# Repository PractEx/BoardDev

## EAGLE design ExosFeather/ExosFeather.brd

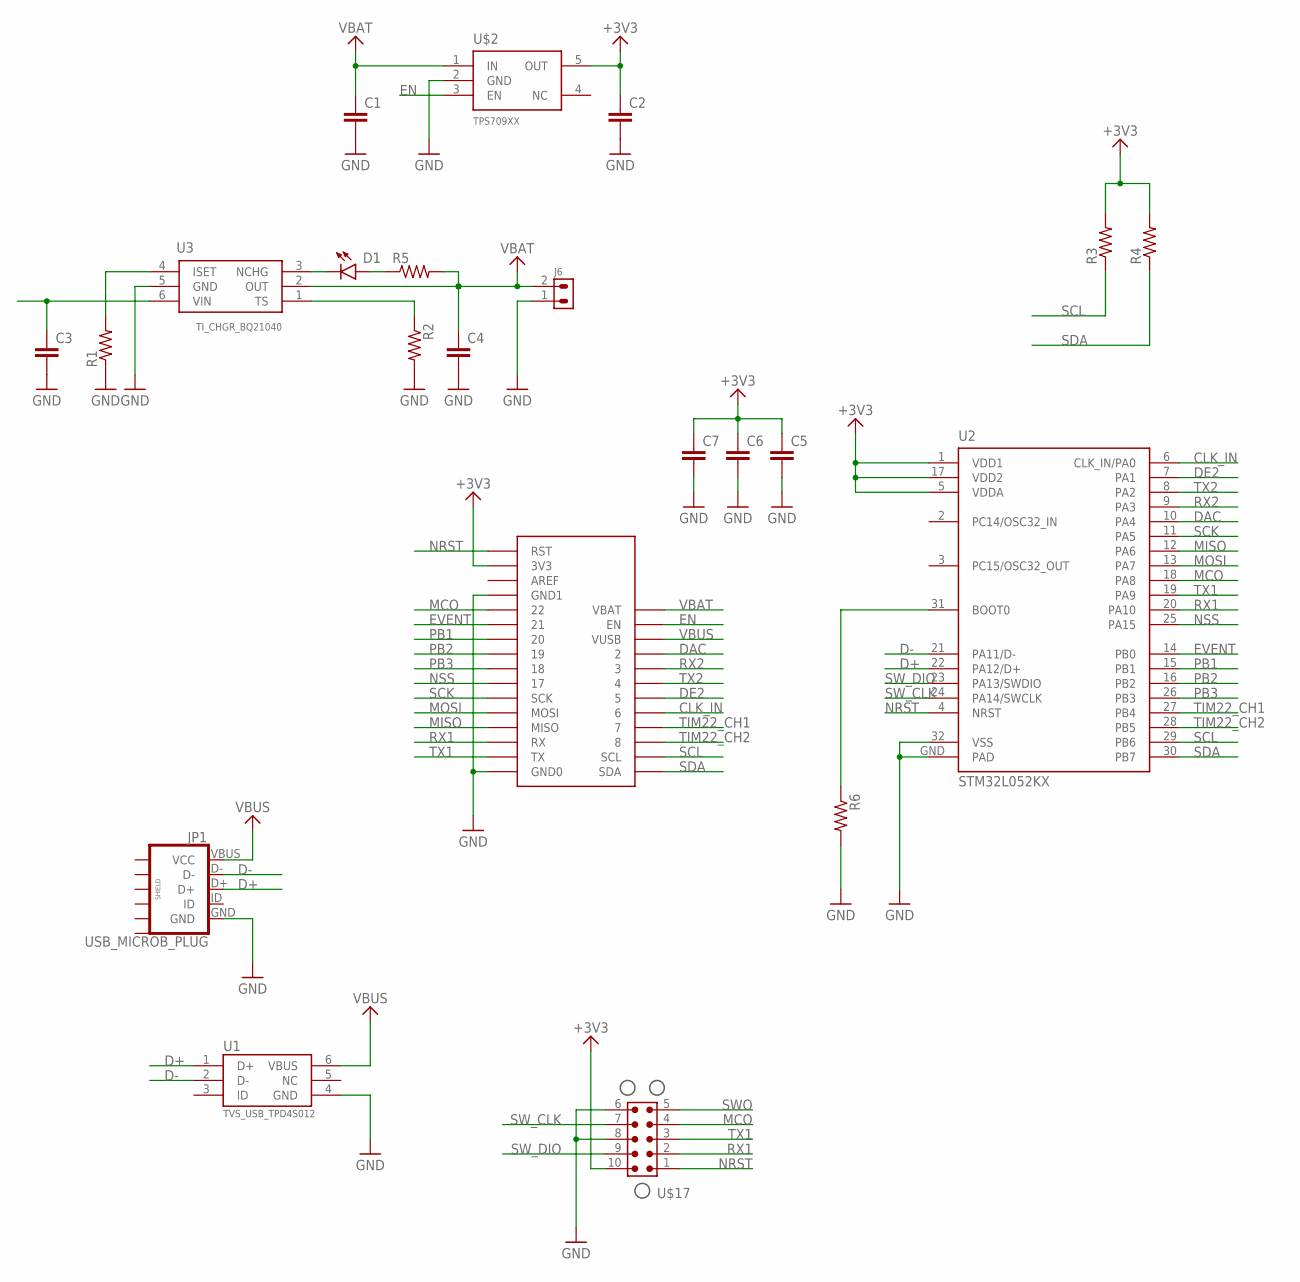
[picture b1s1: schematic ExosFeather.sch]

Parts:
C1, C2, C3, C4, C5, C6, C7: 0603_CAP; 0603
D1: 0603_LED
J6: CONN_2X1_JST_PA
JP1: USB_MICROB_PLUG; USB-MICROB
R1, R2, R3, R4, R5, R6: 0603_RES; 0603
U1: TVS_USB_TPD4S012; USB_TVS_TPD4S012
U2: STM32L052KX; STM32_QFN_32_5X5
U3: TI_CHGR_BQ21040; SOT-23-6_TI
U$1: FEATHER_PINOUT_FULL
U$2: TPS709XX; SOT23-5
U$17: TC_2050_IDC_TOP; TC_2050_IC_TOP

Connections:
+3V3: C2.P$1 (1), C5.P$1 (1), C6.P$1 (1), C7.P$1 (1), R3.P$2 (2), R4.P$2 (2), U2.1 (VDD1), U2.5 (VDDA), U2.17 (VDD2), U$1.P$27 (3V3), U$2.5 (OUT), U$17.10
CLK_IN: U2.6 (CLK_IN/PA0), U$1.P$8 (6)
D+: JP1.D+, U1.1 (D+), U2.22 (PA12/D+)
D-: JP1.D-, U1.2 (D-), U2.21 (PA11/D-)
DAC: U2.10 (PA4), U$1.P$4 (2)
DE2: U2.7 (PA1), U$1.P$7 (5)
EN: U$1.P$2 (EN), U$2.3 (EN)
EVENT: U2.14 (PB0), U$1.P$23 (21)
GND: C1.P$2 (2), C2.P$2 (2), C3.P$2 (2), C4.P$2 (2), C5.P$2 (2), C6.P$2 (2), C7.P$2 (2), J6.1, JP1.GND, R1.P$1 (1), R2.P$2 (2), R6.P$2 (2), U1.4 (GND), U2.32 (VSS), U2.GND (PAD), U3.5 (GND), U$1.P$13 (GND0), U$1.P$25 (GND1), U$2.2 (GND), U$17.6, U$17.8
MCO: U2.18 (PA8), U$1.P$24 (22), U$17.4
MISO: U2.12 (PA6), U$1.P$16 (MISO)
MOSI: U2.13 (PA7), U$1.P$17 (MOSI)
unnamed: R6.P$1 (1), U2.31 (BOOT0)
unnamed: R2.P$1 (1), U3.1 (TS)
unnamed: R1.P$2 (2), U3.4 (ISET)
unnamed: D1.P$2 (C), U3.3 (NCHG)
unnamed: D1.P$1 (A), R5.P$1 (1)
NRST: U2.4 (NRST), U$1.P$28 (RST), U$17.1
NSS: U2.25 (PA15), U$1.P$19 (17)
PB1: U2.15 (PB1), U$1.P$22 (20)
PB2: U2.16 (PB2), U$1.P$21 (19)
PB3: U2.26 (PB3), U$1.P$20 (18)
RX1: U2.20 (PA10), U$1.P$15 (RX), U$17.2
RX2: U2.9 (PA3), U$1.P$5 (3)
SCK: U2.11 (PA5), U$1.P$18 (SCK)
SCL: R3.P$1 (1), U2.29 (PB6), U$1.P$11 (SCL)
SDA: R4.P$1 (1), U2.30 (PB7), U$1.P$12 (SDA)
SWO: U$17.5
SW_CLK: U2.24 (PA14/SWCLK), U$17.7
SW_DIO: U2.23 (PA13/SWDIO), U$17.9
TIM22_CH1: U2.27 (PB4), U$1.P$9 (7)
TIM22_CH2: U2.28 (PB5), U$1.P$10 (8)
TX1: U2.19 (PA9), U$1.P$14 (TX), U$17.3
TX2: U2.8 (PA2), U$1.P$6 (4)
VBAT: C1.P$1 (1), C4.P$1 (1), J6.2, R5.P$2 (2), U3.2 (OUT), U$1.P$1 (VBAT), U$2.1 (IN)
VBUS: C3.P$1 (1), JP1.VBUS (VCC), U1.6 (VBUS), U3.6 (VIN), U$1.P$3 (VUSB)

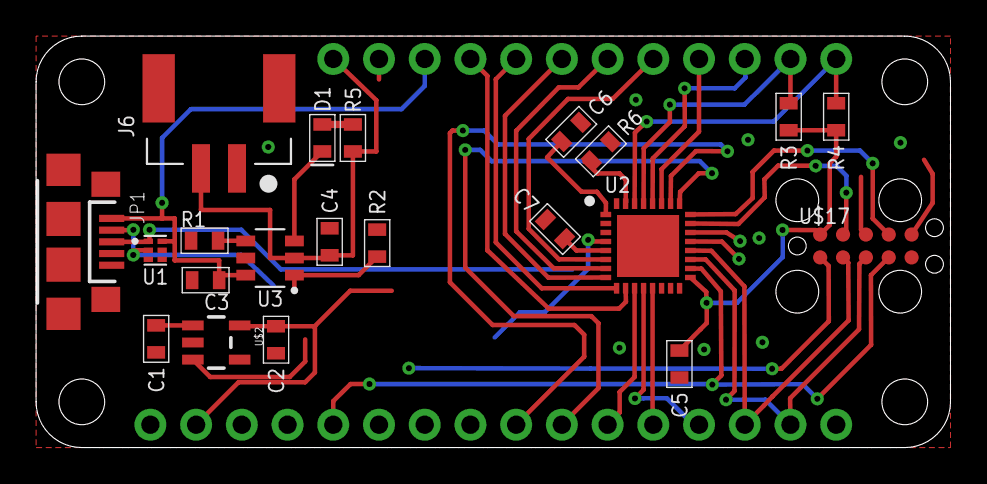
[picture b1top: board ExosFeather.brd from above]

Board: 2 copper layers, 50.8 x 22.9 mm, 22 parts (0 on the bottom side), 35 nets.

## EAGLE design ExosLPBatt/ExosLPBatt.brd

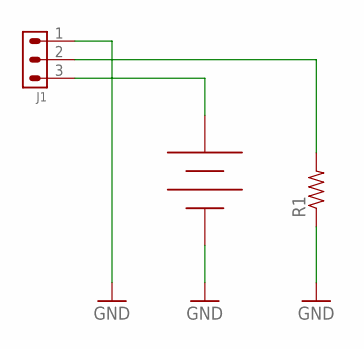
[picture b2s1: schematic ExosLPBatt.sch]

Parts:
J1: CONN_3X1_JST_PA
R1: 0603_RES; 0603
U$2: 14500_KEYSTONE_1024

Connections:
GND: J1.1, R1.P$1 (1), U$2.NEG
unnamed: J1.2, R1.P$2 (2)
unnamed: J1.3, U$2.POS

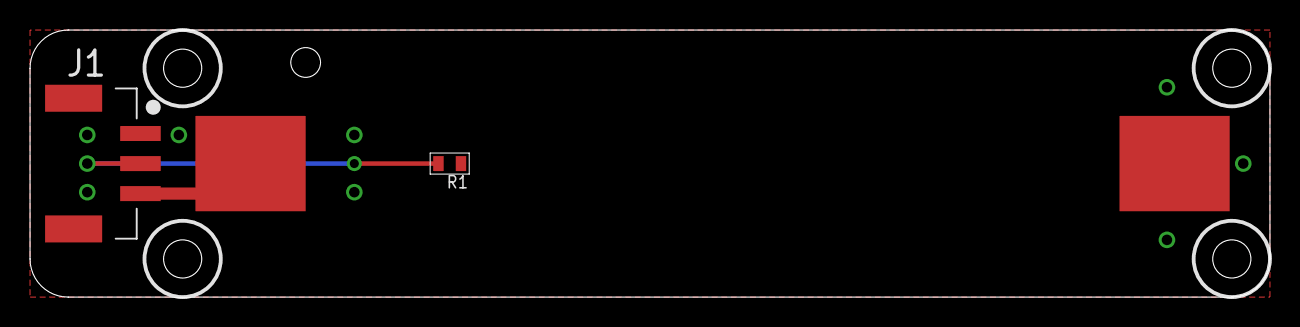
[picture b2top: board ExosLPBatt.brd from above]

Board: 2 copper layers, 82.5 x 17.8 mm, 3 parts (0 on the bottom side), 3 nets.

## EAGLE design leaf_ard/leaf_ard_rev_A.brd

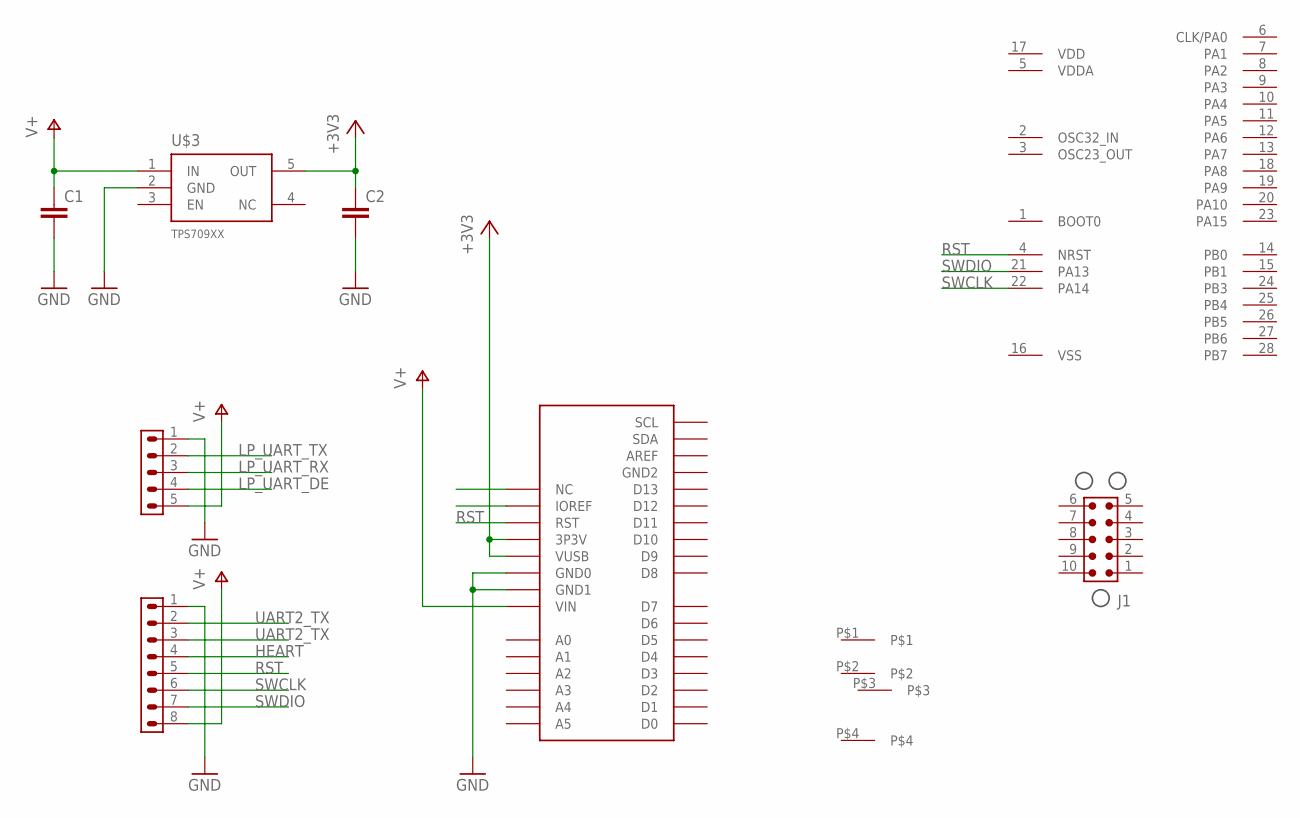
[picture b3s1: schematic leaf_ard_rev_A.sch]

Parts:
C1, C2: 0603_CAP; 0603
J1: TC_2050_IDC_NL_TOP
J2: CONN_5X1_JST_PA
J3: CONN_8X1_JST_PA
U1: STM32L031G6U6; STM32_QFN_28_4X4
U$1: ARDUINO_UNO_R3
U$2: BMI-S-103
U$3: TPS709XX; SOT23-5

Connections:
+3V3: C2.P$1 (1), U$1.P03 (3P3V), U$1.P04 (VUSB), U$3.5 (OUT)
GND: C1.P$2 (2), C2.P$2 (2), J2.1, J3.1, U$1.P05 (GND0), U$1.P06 (GND1), U$3.2 (GND)
HEART: J3.4
LP_UART_DE: J2.4
LP_UART_RX: J2.3
LP_UART_TX: J2.2
RST: J3.5, U1.4 (NRST), U$1.P02 (RST)
SWCLK: J3.6, U1.22 (PA14), U$1.P01 (IOREF)
SWDIO: J3.7, U1.21 (PA13), U$1.P00 (NC)
UART2_TX: J3.2, J3.3
V+: C1.P$1 (1), J2.5, J3.8, U$1.P07 (VIN), U$3.1 (IN)

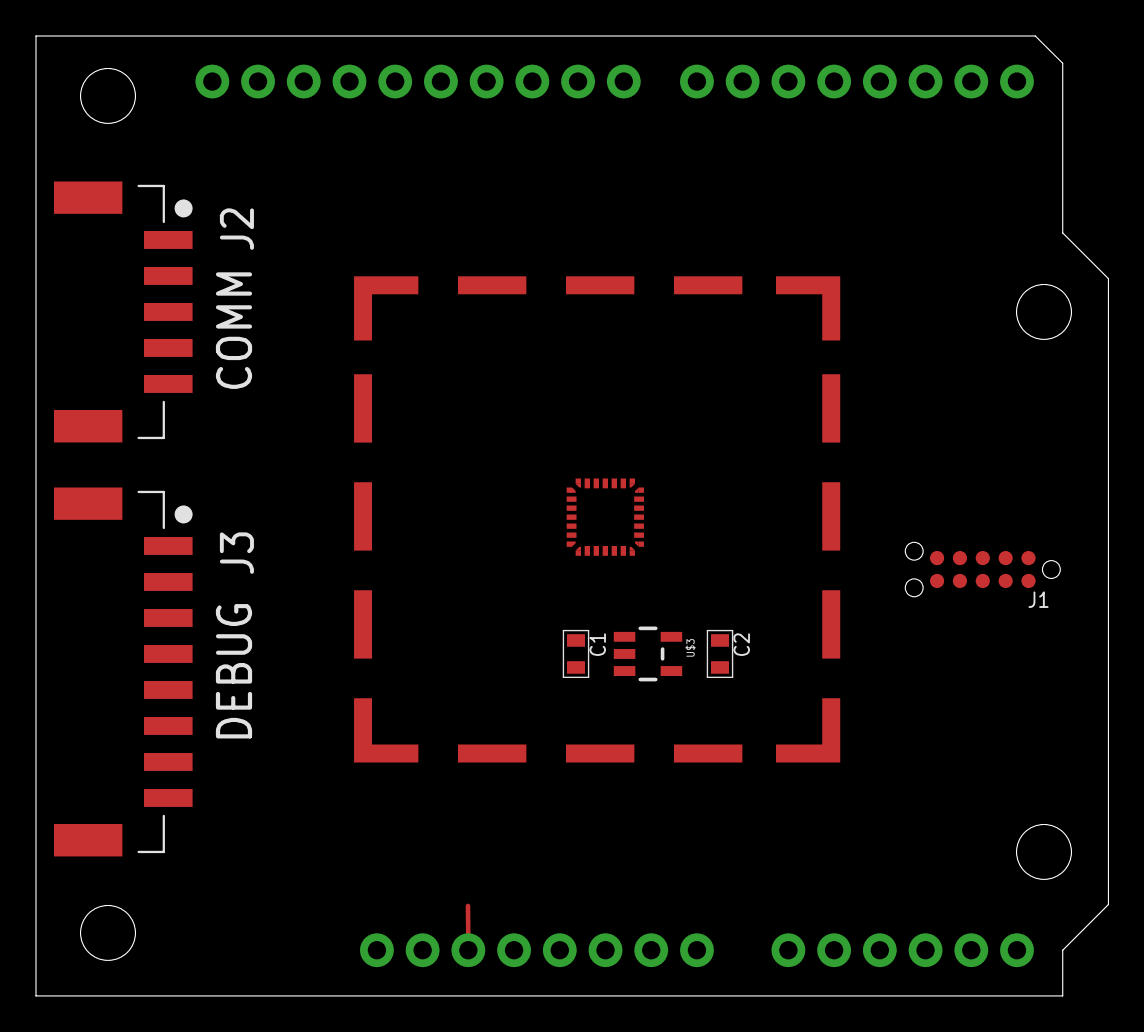
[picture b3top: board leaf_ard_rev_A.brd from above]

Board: 2 copper layers, 59.6 x 53.3 mm, 9 parts (0 on the bottom side), 7 nets.

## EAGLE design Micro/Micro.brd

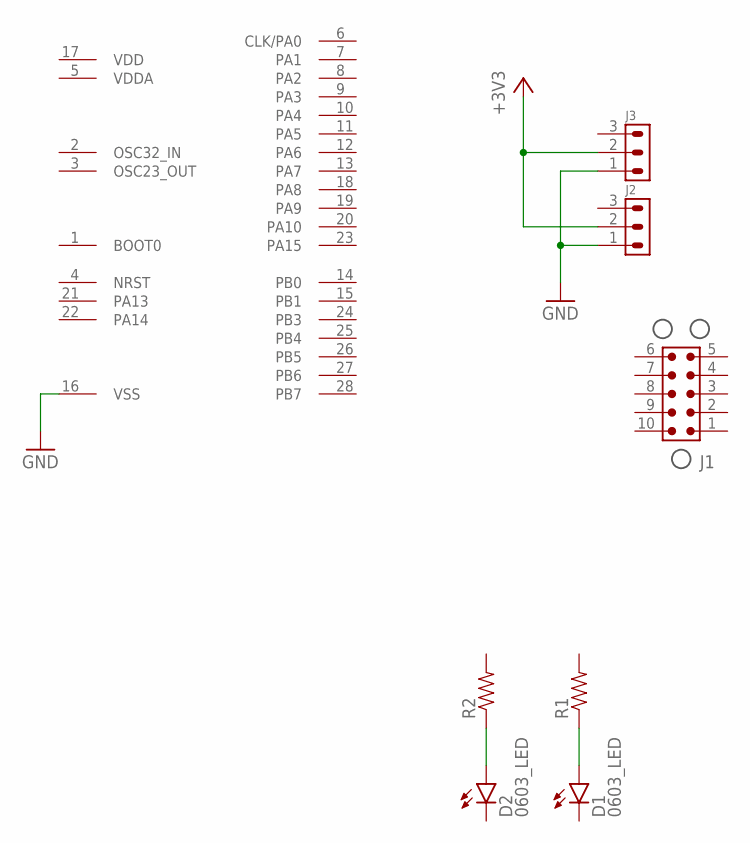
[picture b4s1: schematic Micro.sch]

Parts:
D1, D2: 0603_LED
J1: TC_2050_IDC_NL_TOP
J2: CONN_3X1_LEAF_SMT_INV
J3: CONN_3X1_LEAF_SMT
R1, R2: 0402_RES; 0402
U1: STM32L031G6U6; STM32_QFN_28_4X4

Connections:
+3V3: J2.2, J3.2
GND: J2.1, J3.1, U1.16 (VSS)
unnamed: D1.P$1 (A), R1.P$1 (1)
unnamed: D2.P$1 (A), R2.P$1 (1)

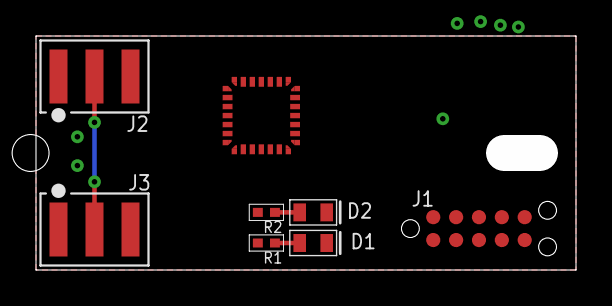
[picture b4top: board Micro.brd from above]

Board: 2 copper layers, 28.0 x 11.0 mm, 8 parts (0 on the bottom side), 4 nets.

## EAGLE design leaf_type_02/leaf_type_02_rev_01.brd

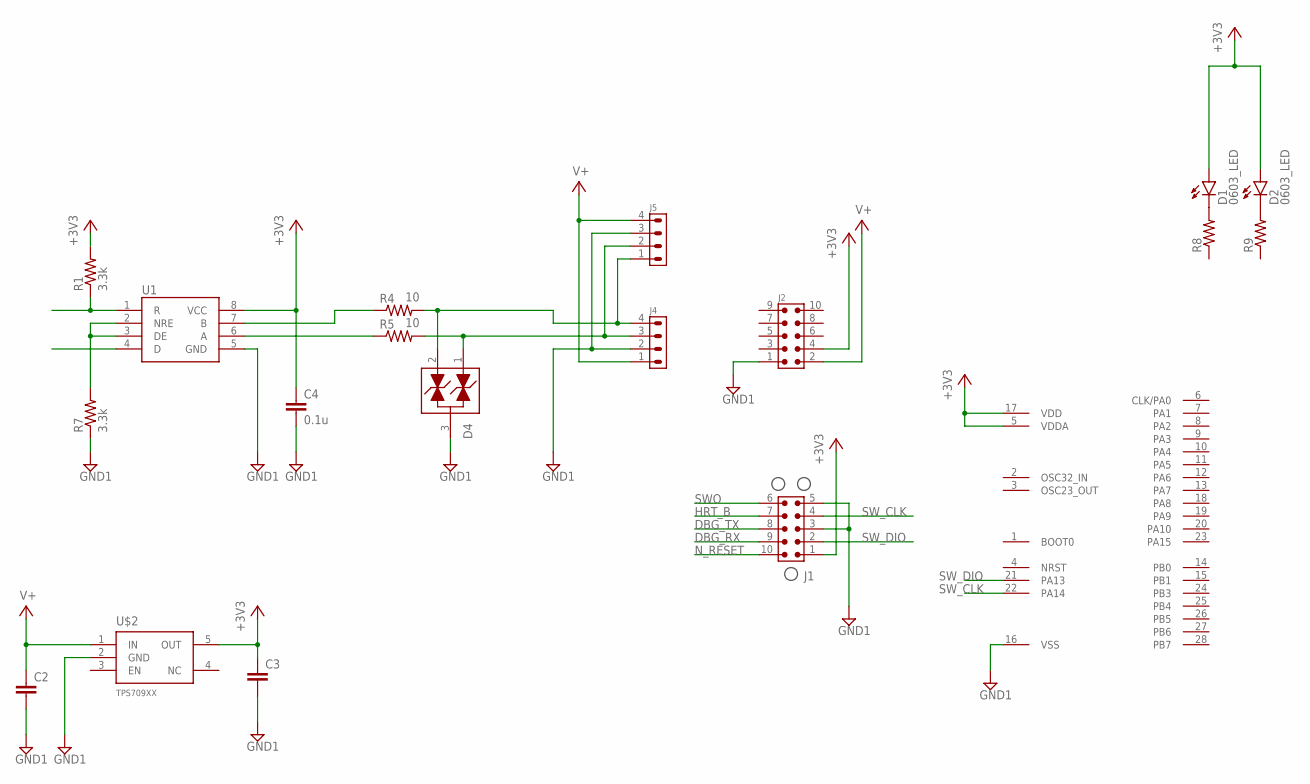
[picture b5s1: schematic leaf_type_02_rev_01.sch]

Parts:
C2, C3: 0603_CAP; 0603
C4: 0.1u; 0603
D1, D2: 0603_LED
D4: TVS_SOT-23; SOT-23_ONSEMI
J1: TC_2050_IDC_NL_TOP
J2: CONN_5X2_0P05_IN_SMT; CONN_5X2_0P050_IN_SMT
J4, J5: CONN_4X1_JST_PA
R1: 3.3k; 0402
R4, R5: 10; 0603
R7: 3.3k; 0603
R8, R9: 0603_RES; 0603
U1: RS485_XCVR_SN65HVD178X; SOIC_08_TI
U2: STM32L031G6U6; STM32_QFN_28_4X4
U$2: TPS709XX; SOT23-5

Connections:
+3V3: C3.P$1 (1), C4.P$1 (1), D1.P$1 (A), D2.P$1 (A), J1.1, J2.4, R1.P$2 (2), U1.8 (VCC), U2.5 (VDDA), U2.17 (VDD), U$2.5 (OUT)
DBG_RX: J1.9
DBG_TX: J1.8
GND1: C2.P$2 (2), C3.P$2 (2), C4.P$2 (2), D4.3, J1.3, J1.5, J2.1, J4.2, J5.3, R7.P$1 (1), U1.5 (GND), U2.16 (VSS), U$2.2 (GND)
HRT_B: J1.7
unnamed: D4.2, J4.4, J5.1, R4.P$2 (2)
unnamed: D1.P$2 (C), R8.P$2 (2)
unnamed: D2.P$2 (C), R9.P$2 (2)
unnamed: R4.P$1 (1), U1.7 (B)
unnamed: D4.1, J4.3, J5.2, R5.P$2 (2)
unnamed: R5.P$1 (1), U1.6 (A)
unnamed: R7.P$2 (2), U1.2 (NRE), U1.3 (DE)
unnamed: R1.P$1 (1), U1.1 (R)
N_RESET: J1.10
SWO: J1.6
SW_CLK: J1.4, U2.22 (PA14)
SW_DIO: J1.2, U2.21 (PA13)
V+: C2.P$1 (1), J2.2, J4.1, J5.4, U$2.1 (IN)

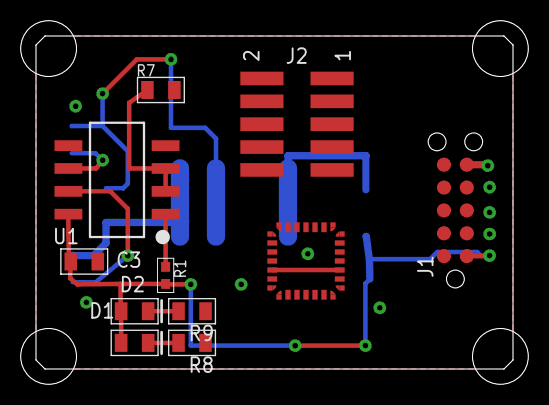
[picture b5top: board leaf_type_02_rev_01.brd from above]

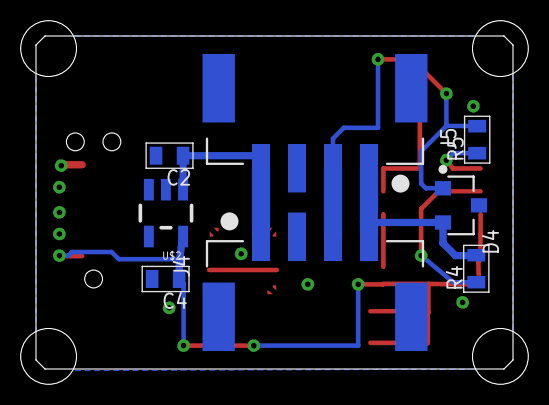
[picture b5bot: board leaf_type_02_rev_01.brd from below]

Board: 2 copper layers, 26.5 x 18.5 mm, 19 parts (8 on the bottom side), 13 nets.

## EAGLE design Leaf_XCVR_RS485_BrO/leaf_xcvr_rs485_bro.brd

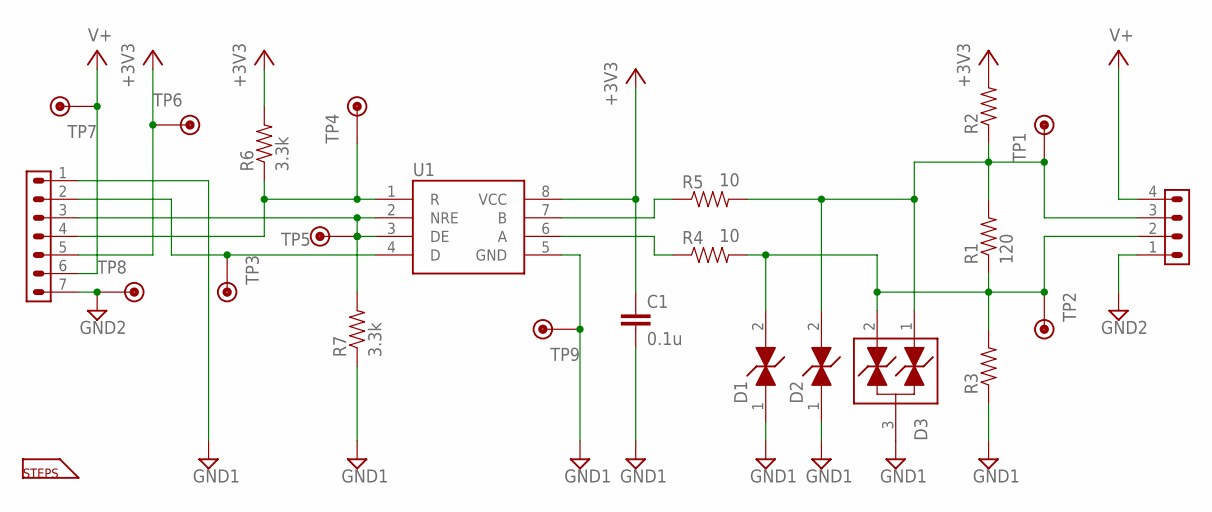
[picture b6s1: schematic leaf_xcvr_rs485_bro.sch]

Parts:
C1: 0.1u; 0603
D1, D2: TVS_DO-214AA; DO-214AA_LITTELFUSE
D3: TVS_SOT-23; SOT-23_ONSEMI
J1: CONN_7X1_JST_PA
J2: CONN_4X1_JST_PA
R1: 120; 0603
R2, R3: 0603_RES; 0603
R4, R5: 10; 0603
R6, R7: 3.3k; 0603
TP1, TP2, TP3, TP4, TP5, TP6, TP7, TP8, TP9: TP1
U1: RS485_XCVR_SN65HVD178X; SOIC_08_TI
U$1: STEPS_LOGO

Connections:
+3V3: C1.P$1 (1), J1.5, R2.P$2 (2), R6.P$2 (2), TP6.P$1, U1.8 (VCC)
GND1: C1.P$2 (2), D1.1, D2.1, D3.3, J1.1, R3.P$1 (1), R7.P$1 (1), TP9.P$1, U1.5 (GND)
GND2: J1.7, J2.1, TP8.P$1
unnamed: R4.P$1 (1), U1.6 (A)
unnamed: R5.P$1 (1), U1.7 (B)
unnamed: D1.2, D3.2, J2.2, R1.P$1 (1), R3.P$2 (2), R4.P$2 (2), TP2.P$1
unnamed: D2.2, D3.1, J2.3, R1.P$2 (2), R2.P$1 (1), R5.P$2 (2), TP1.P$1
unnamed: J1.3, R7.P$2 (2), TP5.P$1, U1.2 (NRE), U1.3 (DE)
unnamed: J1.4, R6.P$1 (1), TP4.P$1, U1.1 (R)
unnamed: J1.2, TP3.P$1, U1.4 (D)
V+: J1.6, J2.4, TP7.P$1

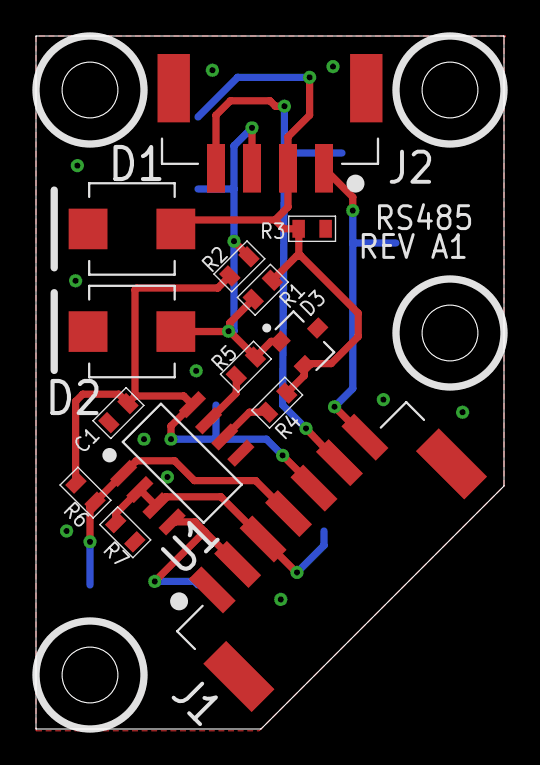
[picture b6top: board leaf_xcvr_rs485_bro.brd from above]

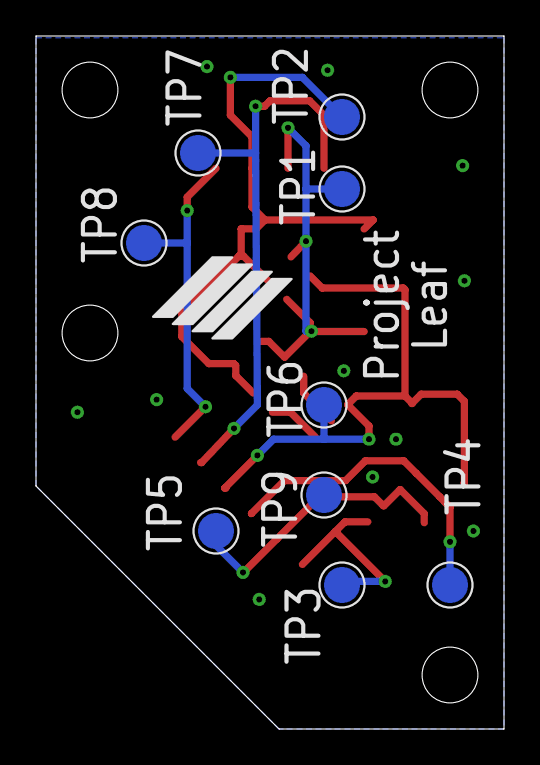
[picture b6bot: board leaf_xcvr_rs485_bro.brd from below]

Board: 2 copper layers, 26.0 x 38.5 mm, 24 parts (10 on the bottom side), 11 nets.

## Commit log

2017-08-10 organizing boards
2017-08-10 tag connect
    committing latest rev of breakout board
2017-08-10 3mm holes
    updated the board to use 3mm standoffs
2017-08-14 update library
    added sn65hvd178x RS485 transciever
2017-08-14 library update
    added symbols for bidirectional and unidirectional TVS diodes
2017-08-14 updating library and xcvr board
    fixed how big the tvs diode symbols are
2017-08-15 new xcvr board for mockups
2017-08-15 working on leafs
2017-08-15 updating rs485 breakout
    added a few new connectors and trying out some new designs
2017-08-16 latest and greatest
2017-08-16 submission to OSHpark
2017-09-06 library add
    added isl rs485 driver and reciever
2017-09-06 updated library & type 02
    fixed some of the sizes of device names, updates rs485 tx & rx drivers
2017-09-07 added to library GH connector and updated 0x02 board layout
    gh connector only can handle 1A which isn't great but very small
2017-09-08 WORK IN PROGRESS
2017-09-14 updating 0x02 build
2017-09-29 stm32 part update
    added stm32l031G6U6 part and added footprints for qfn 28, 32 & tfqp 32
2017-10-19 latest and greatest
    updating for new designs
2017-10-24 exosfeather
    major update
2017-10-25 exosfeather
    updated the pinouts
2017-10-25 exosfeather
    added some new parts
2017-10-25 overwrite error
    accidentally overwrote, mvoing section
2017-10-25 Revert "exosfeather"
    This reverts commit d5dd059b457cfbbf08893ff69975569f2ea8e21c.
2017-10-26 fixing revert of libraries
    see attached
2017-11-07 exofeather update
    latest and greates exofeather
2017-11-10 updating exosFeather
    need to:
    1. add jumpers for enable pin & USB power routing
    2. pin names
    3. decide on PB1 & 2 &3
    4. route enable pin
